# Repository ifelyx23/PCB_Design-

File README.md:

# PCB_Design-
Pin connector prototype

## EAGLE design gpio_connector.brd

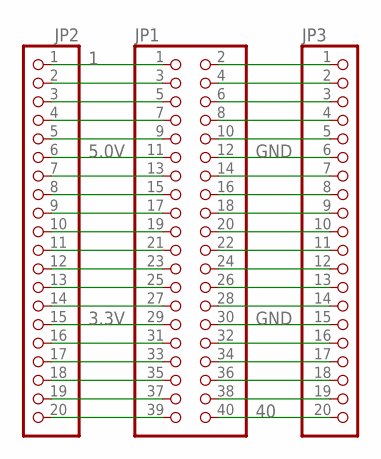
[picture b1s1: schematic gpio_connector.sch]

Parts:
JP1: PINHD-2X20; 2X20
JP2, JP3: PINHD-1X20; 1X20

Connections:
1: JP1.1, JP2.1
3.3V: JP1.29, JP2.15
5.0V: JP1.11, JP2.6
40: JP1.40, JP3.20
GND: JP1.12, JP1.30, JP3.6, JP3.15
unnamed: JP1.2, JP3.1
unnamed: JP1.4, JP3.2
unnamed: JP1.3, JP2.2
unnamed: JP1.5, JP2.3
unnamed: JP1.6, JP3.3
unnamed: JP1.8, JP3.4
unnamed: JP1.7, JP2.4
unnamed: JP1.9, JP2.5
unnamed: JP1.10, JP3.5
unnamed: JP1.13, JP2.7
unnamed: JP1.14, JP3.7
unnamed: JP1.16, JP3.8
unnamed: JP1.15, JP2.8
unnamed: JP1.17, JP2.9
unnamed: JP1.18, JP3.9
unnamed: JP1.20, JP3.10
unnamed: JP1.19, JP2.10
unnamed: JP1.21, JP2.11
unnamed: JP1.22, JP3.11
unnamed: JP1.24, JP3.12
unnamed: JP1.23, JP2.12
unnamed: JP1.25, JP2.13
unnamed: JP1.26, JP3.13
unnamed: JP1.28, JP3.14
unnamed: JP1.27, JP2.14
unnamed: JP1.32, JP3.16
unnamed: JP1.34, JP3.17
unnamed: JP1.33, JP2.17
unnamed: JP1.31, JP2.16
unnamed: JP1.35, JP2.18
unnamed: JP1.37, JP2.19
unnamed: JP1.39, JP2.20
unnamed: JP1.38, JP3.19
unnamed: JP1.36, JP3.18

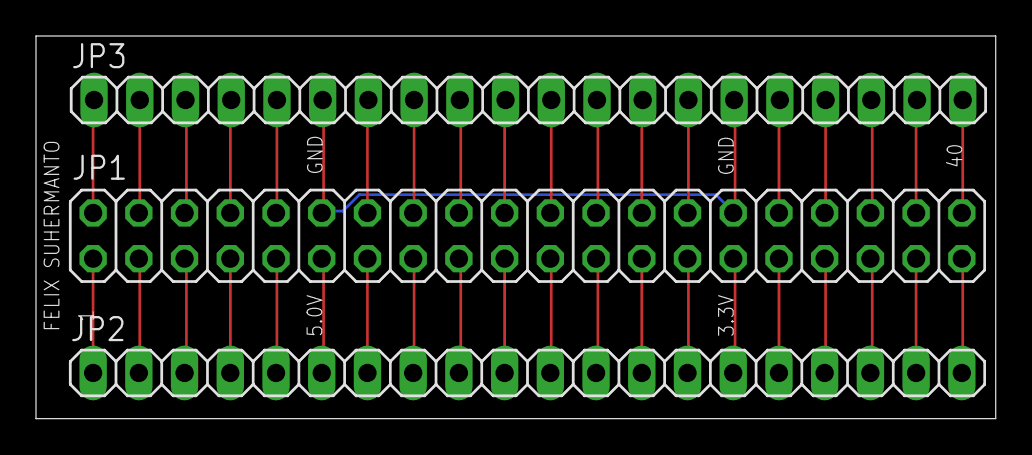
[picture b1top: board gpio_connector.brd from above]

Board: 2 copper layers, 53.3 x 21.3 mm, 3 parts (0 on the bottom side), 39 nets.

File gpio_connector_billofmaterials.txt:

Partlist exported from C:/Users/Felix Suhermanto/Documents/eagle/GPIO_CONNECTOR/gpio_connector.sch at 4/25/2018 3:34 PM

Part Value Device     Package Description 
JP1        PINHD-2X20 2X20    PIN HEADER  
JP2        PINHD-1X20 1X20    PIN HEADER  
JP3        PINHD-1X20 1X20    PIN HEADER
